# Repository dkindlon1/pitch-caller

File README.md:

# Pitch Caller

A pitch-calling engine for baseball coaches who don't know sequencing well. Each pitch it puts down a sign and a
spot (pitch type plus one of six targets), chosen at random from a mix weighted toward the calls that give up the
fewest expected runs. The mix keeps it hard to read. It tracks the pitcher's confidence in each pitch, learns each
hitter during the game, and flags when the pitcher may be done.

Levels: high school, college D3, college D1, and pro tables for comparison.

## How it decides

    Cost(pitch, spot | situation) = sum over outcomes  P(outcome) x [runs now + run value of the next state]

- **Run values** by level from real data: MLB 2010-15, 2026 NCAA conference team stats (D1, D3), MaxPreps 2026
  national varsity averages (high school). See `college_rates.py`, `hs_rates.py`, `run_tables.py`.
- **Outcome model**: where the pitch lands (command, confidence, level wildness, whether it's landing today), then
  swing, whiff, called strike, foul, contact quality, hit by pitch, wild pitch. Fitted so simulated games
  reproduce each level's real strikeout, walk, HBP and hit rates (`calib.py`, `fit_all.py`, `outcome_params.py`).
- **Calls**: each at-bat is solved once over count x the hitter's look, with the hitter's guess (what he's sitting on)
  settled at each count; the call is drawn from the low-cost calls inside a never-pick window, and randomness scales
  with the stakes of the count.
- **Coach rules built in**: get it over with off-speed only when that pitch is landing today; attack the zone at
  2-2; never re-call what he just shook off; nothing below the pitcher's trust line while he trusts something.

## The engine: v1.0, one version

There is one engine, with no flags or modes, in Python (`engine.py`, the reference) and JavaScript (`app/engine.js`,
copied to `web/lib/`). It is v0.8's at-bat planning (below) plus the v0.9 terms and the v1.0 fixes and fits
(`docs/PLAN_v1.0_2026-11-09.md`, build log `docs/BUILD_v1.0_REPORT.md`). `golden/golden_v10.py` and
`golden/golden_v10.js` check Python and JavaScript against one frozen reference (500 cases); `golden/fast.py` compares
the two live. The v0.7c call path and the other v0.9 leftovers were removed in v1.0 Step 6.

## Planning the at-bat (from v0.8)

v0.8 (spec: `docs/SPEC_v0.8.md`, amendments in its section 12) keeps the cost equation and adds what a pitching coach
thinks about between pitches:

- **What he's sitting on.** The hitter guesses a pitch and a height; the engine and the hitter settle at a
  quantal-response balance point each count, and a "fooled" read shifts his guess for the rest of the at-bat.
- **Planning ahead.** Each at-bat is solved once over count × the hitter's look (the speed and height he's tuned to),
  so a pitch is valued for what it sets up. A guardrail keeps every call within 0.010 runs of the best call on its own.
- **Timing, eye level, repeats, familiarity** by class from earlier at-bats today (replacing v0.7c's pairing and
  batters-faced terms), with Statcast-fitted sizes (`seq_fit.py`, `fit_v08.json`): timing surprise ships at half the
  guess, a change of eye level slightly *hurts* in MLB data, and tunneling ships on chase swings only (v1.0 D5:
  `beta_tun_chase` 0.310 fitted, `beta_tun_whiff` 0; the tunnel score showed no effect on whiffs).
- **The game situation.** Win expectancy and leverage tables (`we_tables.py`) blend runs with winning late in close
  games; typed batted balls with runner-on-third and double-play rules; the running game; an intentional-walk
  suggestion.
- **Today's umpire**, fatigue (speed and stuff, or radar), hitter grades (contact, power, eye) learned across games.
- **A why line** on every call.

Checks: `golden/golden_v10.*`, `tests.py`, `tests_v09_followups.py`, `readthrough/scenarios.py`, `app/budget_v08.js`,
`app/v08_e2e.js`. The v0.7c and v0.8 engines and their golden files are gone (v1.0 Step 6); `golden/golden_v09.json` stays as the historical v0.9 reference and the source of the golden inputs.
Build report (v0.8): `docs/BUILD_v0.8_REPORT.md`.

## Known limits (v1.0)

- **Runner advancement (#23, D10, skipped for 1.0):** a non-double-play ground out doesn't move a runner from first to
  second, and a single doesn't take a runner from first to third. Small run-value gaps; the simulator shares them.
- **Side-blind misses (D6, deferred):** a missed pitch misses up/down and in/off the zone, never specifically arm side or
  glove side.
- **Familiarity (#26, dropped):** the within-game familiarity term stays as fitted; the claim that it "erases the pitch"
  did not reproduce, and in-game hitter memory has one owner (#7).

## Watch prototype (opt-in)

Pitcher and catcher wristbands on Bangle.js 2 (plan: `docs/plans/PLAN_watch_prototype_2026-11-15.md`, review:
`docs/REVIEW_watch_prototype_plan_2026-11-15.md`). The coach taps **Accept** under the call (or Enter) and both watches show
the sign and the spot in words; a recorded pitch, a shake-off, his own call, undo or the third out clears them. Only where
the browser has Web Bluetooth (Chrome on a computer or Android) and the device opted in by opening the game app once
with `?watch=1` (`?watch=0` turns it off); everywhere else, the iPad included, nothing changes.

| File | What it is |
| --- | --- |
| `app/watch.js` | The link: up to two watches, one write queue each, message numbers, receipts and retries, reconnect, soak mode |
| `watch/bangle/pitchiq.app.js` | The watch app (its own Bluetooth service, data not code); install steps in `watch/bangle/README.md` |
| `app/watch_test.js`, `watch/bangle/test.js`, `app/watch_e2e.js` | The link against fake watches running the real watch core; the watch app against stand-in firmware; the page |

## Files

| File | What it is |
| --- | --- |
| `engine.py` | The engine, v1.0 (the reference; `app/engine.js` is its JavaScript twin): the at-bat solve and live call (`call_v08`), the outcome model, coach rules, the why line and intent label; one grade point = one SD of real pitchers (and hitters) at the level |
| `pitcher_lines.py`, `talent_spread.py`, `fit_spread.py`, `spread_params.py`, `spread_test.py` | Spread calibration: real 2026 per-pitcher lines, the true spread between pitchers, the fitted scales, and the check |
| `flags.py` | "Time for a change" flag |
| `simulate.py` | Full-game simulator with hidden hitter traits and pitch off-days; presets for pitcher and lineup types |
| `review.py` | Grades every call against coaching rules (wrong / questionable) and measures predictability |
| `batch.py`, `regrade.py`, `inputs_report.py` | Run many games and summarize them |
| `college_rates.py`, `hs_rates.py`, `run_tables.py` | Run values from real stats |
| `calib.py`, `fit_all.py`, `refit_mlb.py` | Fit the outcome model to real rates |
| `tests.py` | Regression checks (42 in v1.0), including the predictability grid (`grid_v10.py`) |
| `statcast_check.py` | The hitter-vs-pitch model against MLB Statcast pitches, by attack zone and count (`results/statcast_check.txt`) |
| `fuzz.py` | 29 logic and learning checks on thousands of random situations |
| `matrix/` | 21-setup test matrix: levels, pitcher types, lineups, input levels, shake-offs, coach overrides |
| `results/` | Latest logic-check and matrix reports |
| `app/` | Tablet prototype: `engine.js` (JavaScript port, verified against Python), `index.src.html`, built page in `dist/` |

## Run it

Python 3.11+ with `numpy` and `scipy`. Node 18+ for the app checks (Playwright for the browser test).

    python3 tests.py                                     # regression checks (42)
    python3 spread_test.py                               # calibrated spread between pitchers (about 2 minutes)
    python3 fuzz.py 3000 300                             # logic and learning checks
    LEVEL=college_d3 python3 batch.py runs/d3 1 10        # 10 simulated D3 games, graded
    STAFF=power LINEUP=fb_mashers LEVEL=hs python3 batch.py runs/x 1 10
    ./matrix/run.sh && python3 matrix/report.py           # the full matrix (about an hour)

    python3 golden/fast.py 40 && node golden/golden_v10.js  # JS engine must match Python exactly
    cd app && python3 build.py                             # builds dist/pitch-caller.html
    node app/smoke.js                                      # drives the page in a browser (from the repo root)

Simulator settings (environment variables): `LEVEL` (hs, college_d3, college_d1, mlb), `STAFF` (default, power,
finesse, two_pitch, lefty, four_pitch, shaky), `LINEUP` (default, strong, weak, lefty_heavy, switch, fb_mashers,
os_killers, late), `INPUTS` (1 results only, 2 plus contact, 3 plus hitter reads, 4 plus measured movement),
`NOISE` (share of optional entries logged wrong), `TRUE_MOVE`, `SHAKE`, `OVERRIDE`.

## Database and learning (app/)

Everything lives on the device in IndexedDB (`app/db.js`): our team, pitchers with their arsenals, catchers, opponents
and their hitters, pre-game check-ins, TrackMan/Rapsodo sessions, games, every pitch thrown, and the learned models.
Records carry ids and timestamps and are soft-deleted, so a sync service (Supabase or similar) can be added later
without changing the data. Back up and Restore on the Roster screen write and merge a JSON file (newer edits win).

**Every logged pitch stores** the pitcher, pitch, hitter, catcher, target, result, where it ended up (if logged), the
exact situation and inputs the engine used, and what the engine expected to happen.

**The flywheel** (`app/learner.js`, learner v2, spec in `docs/LEARNING_SPEC.md`): after End game, every pitch he has
thrown is replayed against what the engine expected, and each pitch's command and stuff are tracked game by game
(starting from the coach's grades, allowing for drift, a new season and changes the coach marks). The calls move toward
what's learned at most 0.15 a game and never more than 1.0 from the coach's grade unless he accepts a flag. Big
disagreements are flagged, not applied. A scoreboard compares learning with the coach's grades and switches learning off
if it predicts worse. Only the engine's own calls teach it. Hitters carry what they did against what the engine expected
across games. Check-ins set the day's starting feel per pitch and can lower his fatigue point.

**Imports** (`app/import.js`): TrackMan CSVs by its documented column names; Rapsodo by loose name matching (check the
first real file). Break and release side are normalised to arm side positive using his fastballs. Opponent hitter sheets.

| File | What it is |
| --- | --- |
| `app/db.js` | Database: stores, backup/restore, migration from the old saved state |
| `app/learn.js` | Learner v1 (now only check-ins, predictions and logging helpers in the app; its limits fixed in 1.1.0) |
| `app/import.js` | TrackMan, Rapsodo and hitter-sheet import |
| `app/roster.js` | Database glue and the Roster screen (inlined into the page by `build.py`) |
| `app/learn_test.js`, `db_test.js`, `import_test.js` | Node checks (`db_test.js` needs `npm i fake-indexeddb`) |
| `app/db_e2e.js` | Browser test of the whole loop, served over http; screenshots in `app/e2e_shots/` |
| `app/learner.js`, `app/worker.js` | Learner v2 (spec in `docs/LEARNING_SPEC.md`): replay, talent filter, traits, caps, flags, scoreboard. Drives the calls; runs after End game in a background worker. No trait passes the gate on v0.7b/c, so traits are off |
| `app/travel_e2e.js` | Browser check: travel ball in Setup, calls at that level, a coach's chase call at 3-1 graded against the rule |
| `app/replay_e2e.js`, `app/replay_check.js` | Proof that a charted game replays exactly from the raw log (browser game, then any backup) |
| `app/shadow.js`, `app/sim_backup.js` | Learner v2 scored against the coach's grades and what the app served, on a backup; seasons charted through the app from a hidden true pitcher |
| `app/worlds.js`, `app/worlds_test.js` | Simulated seasons played pitch by pitch, and the 13 worlds checks for learner v2 |
| `app/gate_test.js`, `app/gate_result.json` | The trait gate and its latest result |
| `app/same_engine_test.py` | Proves engine v0.7 with no traits and spread scales at 1 is identical to v0.6f (needs the old engine file as an argument) |

    cd app && node learn_test.js && node db_test.js && node import_test.js
    python3 build.py && node db_e2e.js

## Status

**Nov 6:** one engine, v0.9, no flags. See the top of this file and `docs/FOLLOWUPS_v0.9_REPORT.md`. The history below
is kept as it was.

Engine v0.7c (2026-11-03): 3-0 gets the tightest mix (an average arsenal throws about two fastballs in three there),
learning mode is scored the way calls are made, travel ball is a level (high school tables), impossible input gets a clear
error. Regression 19 of 19, logic 27 of 29 (same two explained), parity, spread, worlds 13 of 13, app tests all pass.

**Statcast check** (`statcast_check.py`, 2025 MLB, about 86,000 pitches): the engine's run values per zone are close in
many spots, but its hitter model is too flat. It has about half the real swing-and-miss rate in every zone and makes up
the strikeouts with too many chase swings, and in pitcher's counts it charges off-speed over the heart about a third of
what real hitters do (0.016 runs more than the edge, real 0.045). That's why "middle" stays in the two-strike mix.
Not yet refit.

Tested in simulation only. Engine v0.7b (spec section 18): command and stuff spread and the walk/strikeout link match
real 2026 pitchers; no chase target at 3-0 or 3-1. Regression checks 17 of 17, logic checks 27 of 29 (the two failures
are explained in the spec), learner worlds 13 of 13, spread checks all pass; reduced matrix (6 setups × 4 games) wrong
calls 0.3-4.9%. Open: amateur hitters' swing and chase behavior
is assumed MLB-like until real pitch-by-pitch data is available; HS spread is estimated from D3.

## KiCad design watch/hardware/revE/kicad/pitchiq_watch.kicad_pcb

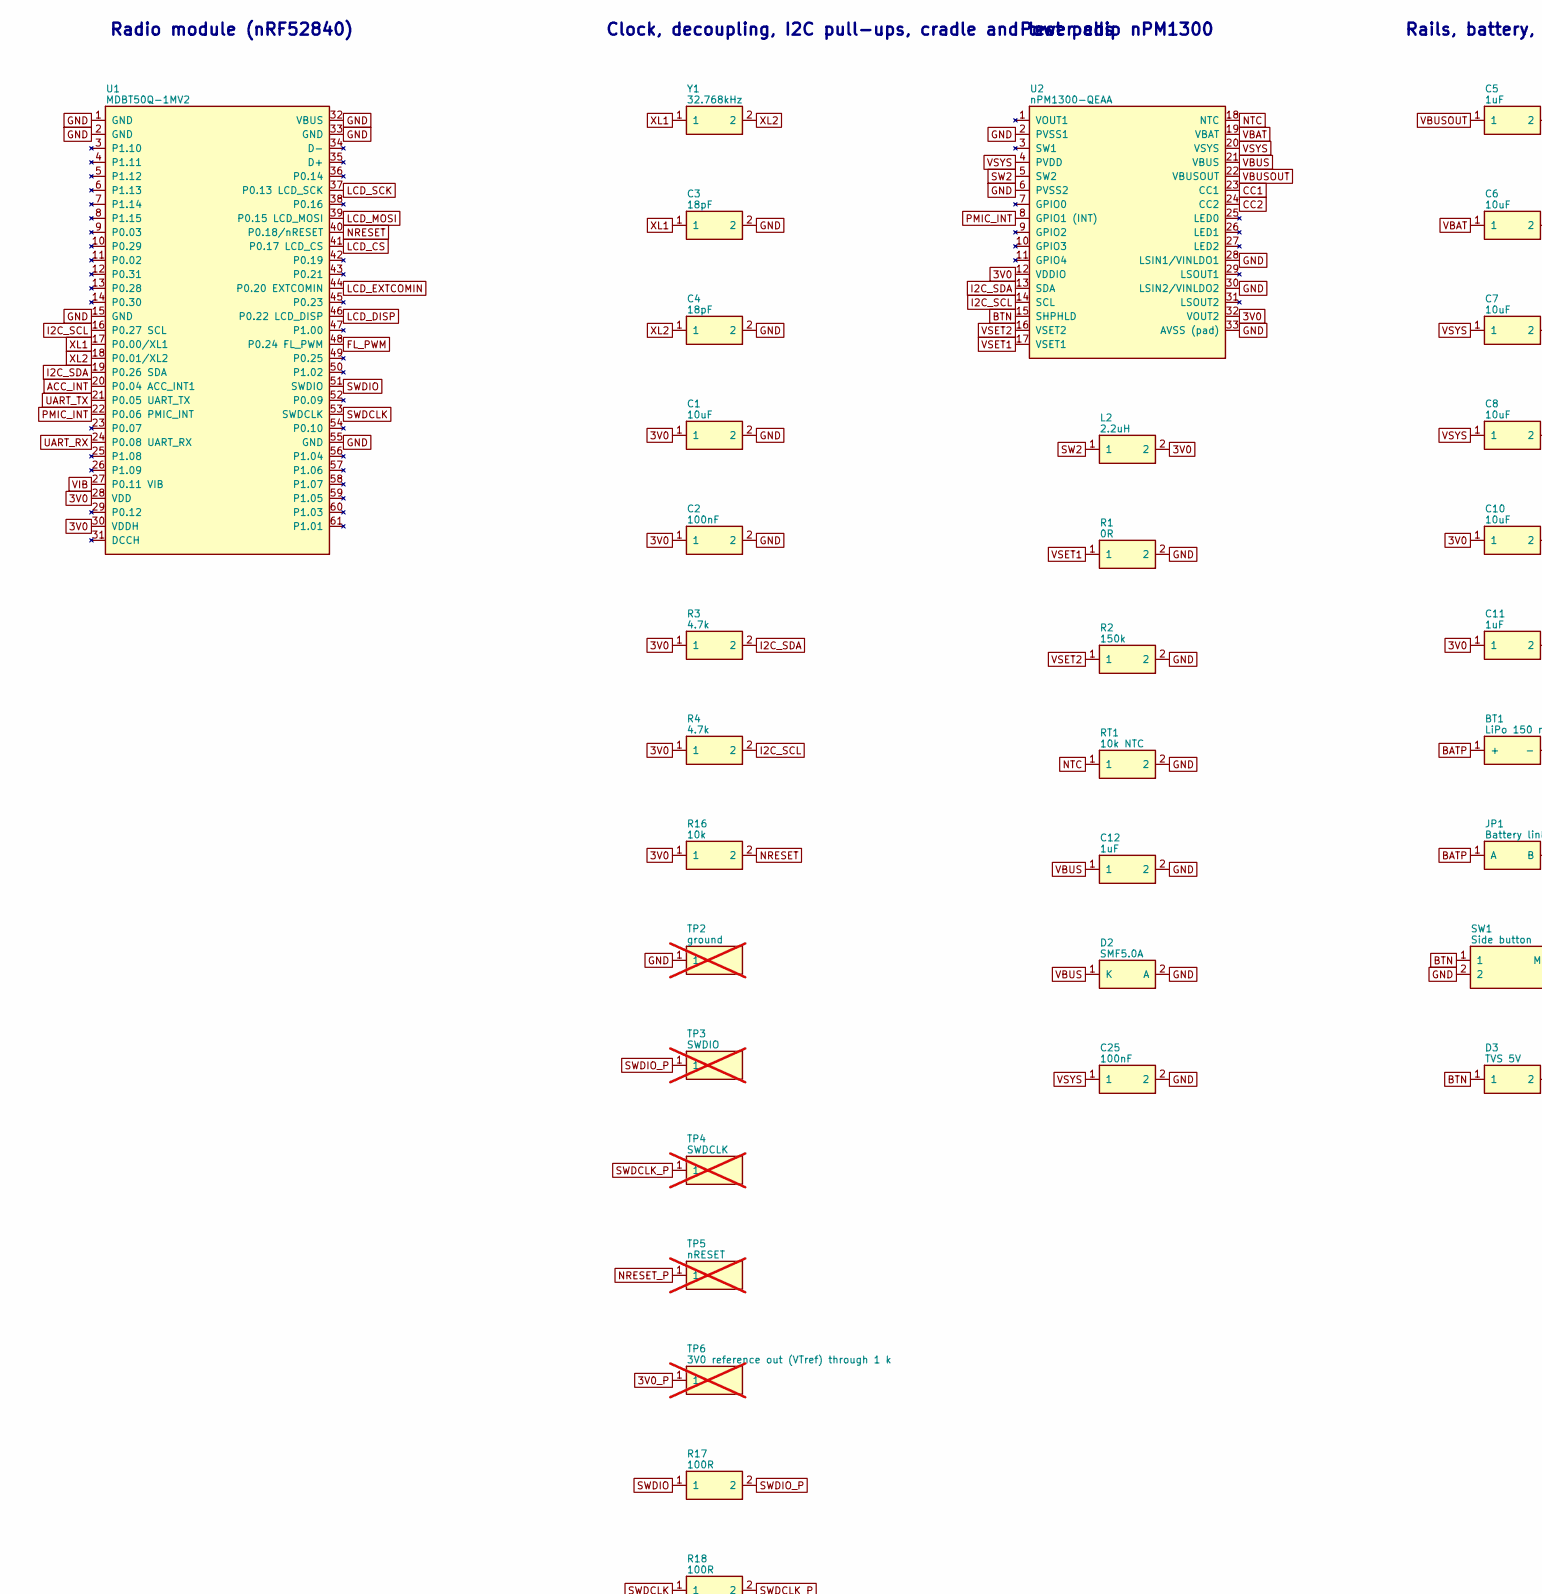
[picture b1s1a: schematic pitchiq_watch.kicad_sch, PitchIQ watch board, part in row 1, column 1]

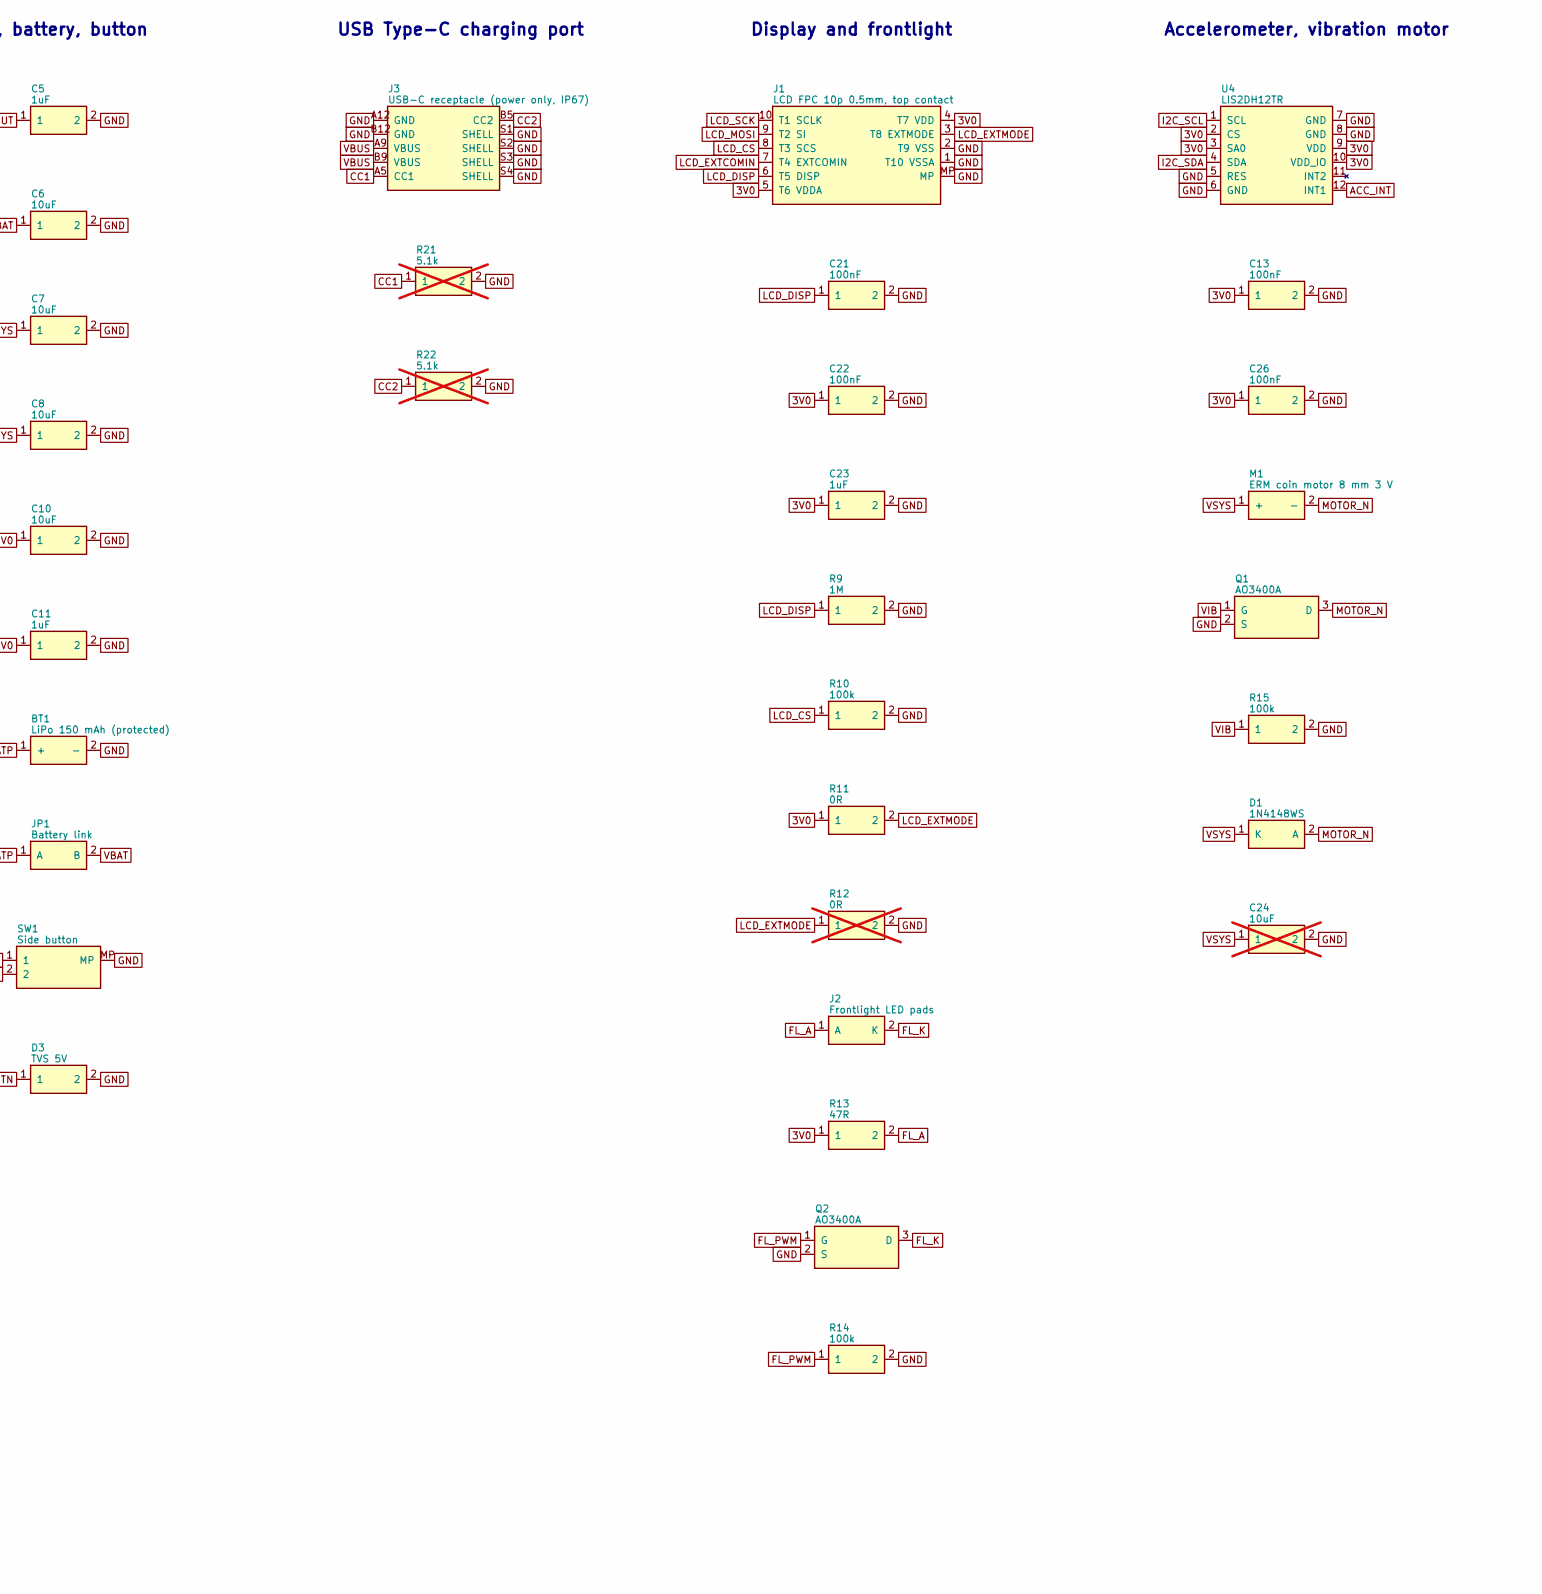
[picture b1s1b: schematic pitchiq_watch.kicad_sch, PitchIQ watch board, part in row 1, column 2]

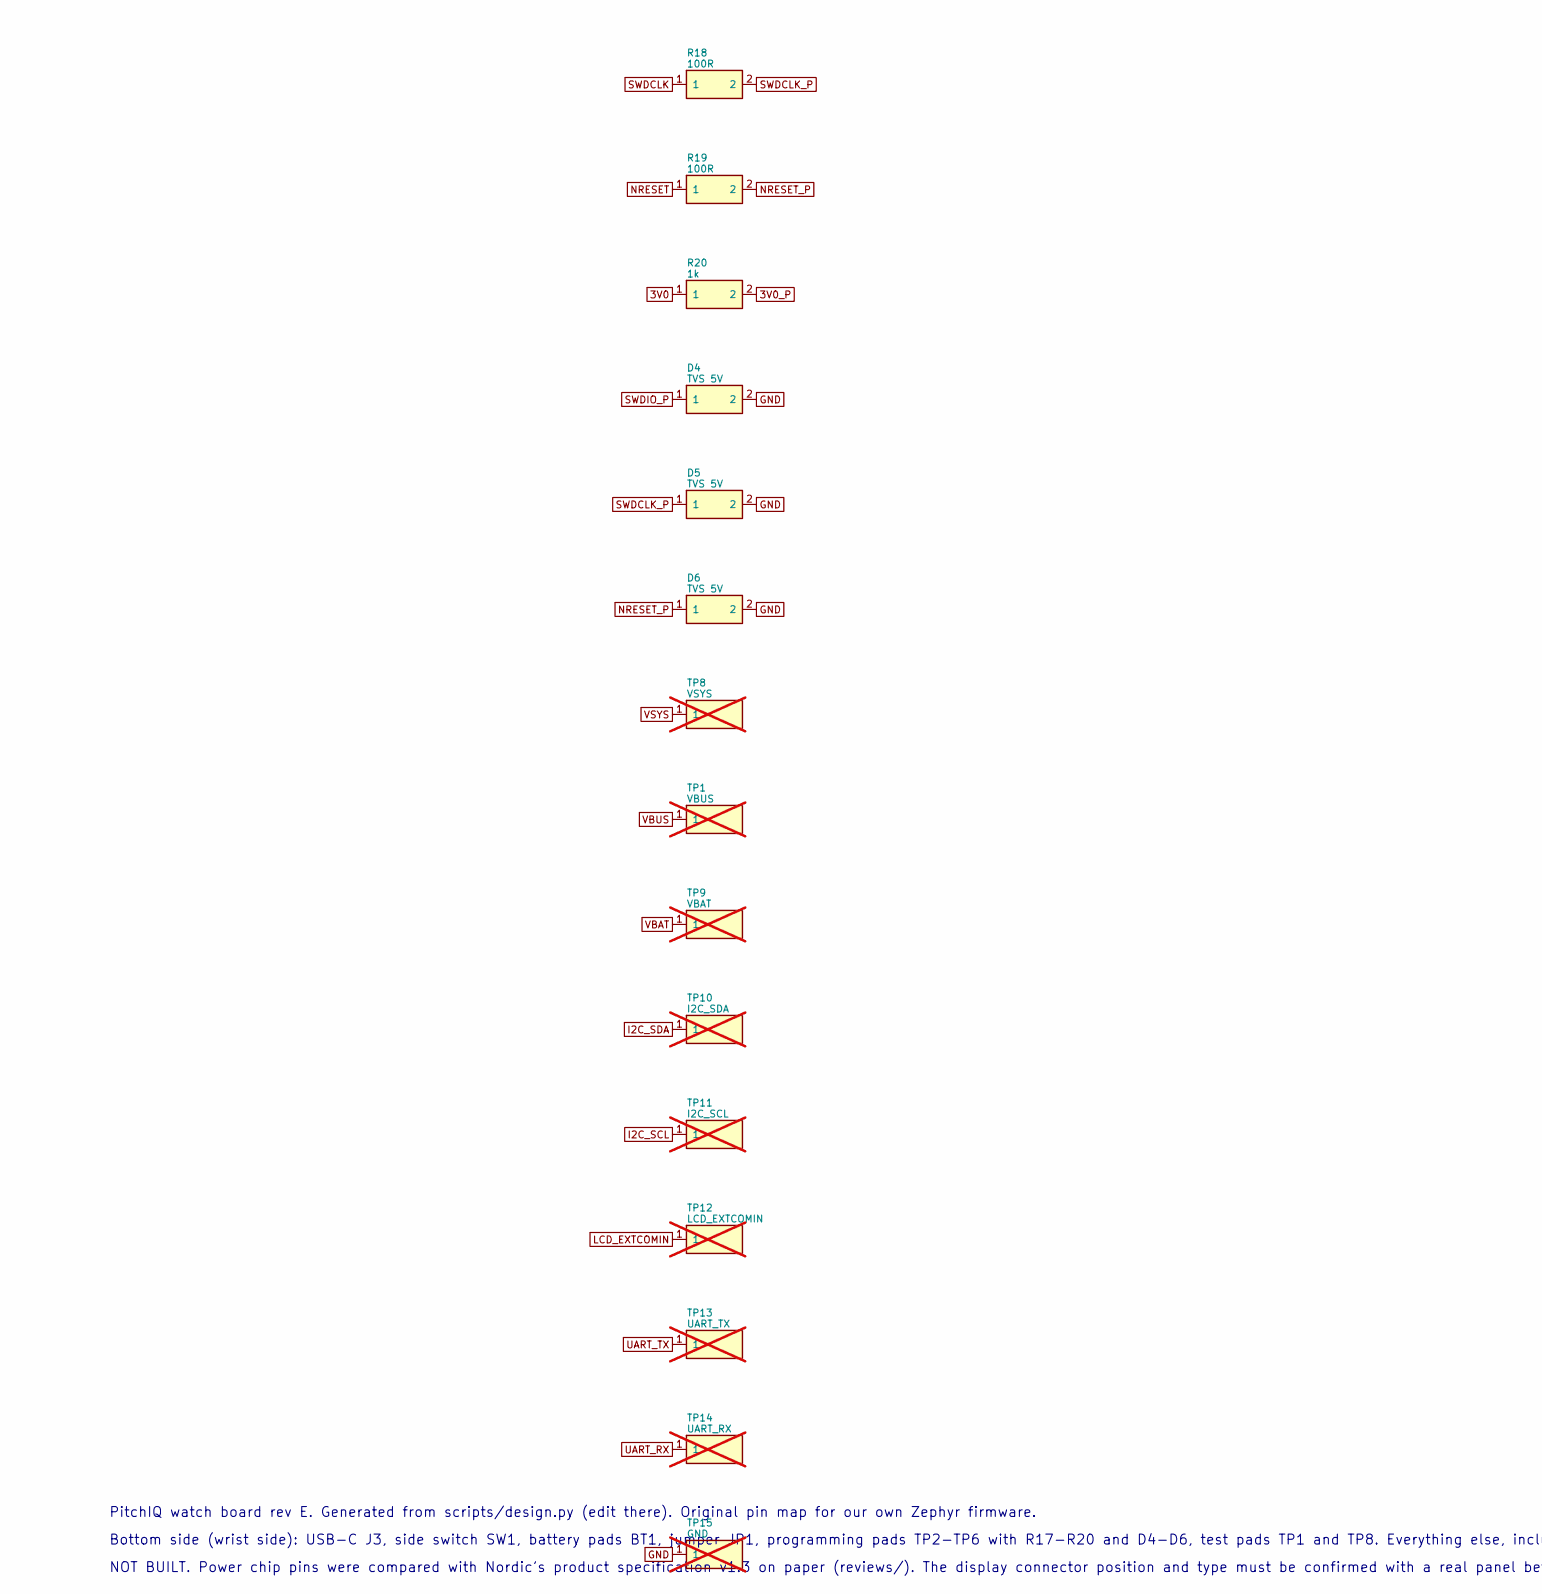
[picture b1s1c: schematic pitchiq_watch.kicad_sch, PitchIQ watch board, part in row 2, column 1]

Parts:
BT1: LiPo 150 mAh (protected); Pad_2x_wire; MPN 1317
C1, C6, C7, C8, C10: 10uF; C_0603_1608Metric; MPN CL10A106MA8NRNC; LCSC C96446
C2, C13, C21, C22, C25, C26: 100nF; C_0402_1005Metric; MPN CL05B104KO5NNNC; LCSC C1525
C3, C4: 18pF; C_0402_1005Metric; MPN CL05C180JB5NNNC; LCSC C307443
C5, C11, C12, C23: 1uF; C_0402_1005Metric; MPN CL05A105KA5NQNC; LCSC C52923
C24: 10uF; C_0603_1608Metric; MPN CL10A106MA8NRNC; LCSC C96446; not fitted
D1: 1N4148WS; D_SOD-323; MPN 1N4148WS; LCSC C2128
D2: SMF5.0A; D_SOD-123F; MPN SMF5.0A; LCSC C151296
D3, D4, D5, D6: TVS 5V; D_SOD-323; MPN PESD5V0S1BA; LCSC C2985486
J1: LCD FPC 10p 0.5mm, top contact; Hirose_FH12-10S-0.5SH_1x10-1MP_P0.50mm_Horizontal; MPN FH12A-10S-0.5SH(55)
J2: Frontlight LED pads; Pad_2x_wire_small; MPN (pads only)
J3: USB-C receptacle (power only, IP67); USB4715; MPN USB4715-GF-A; LCSC C6906846
JP1: Battery link; SolderJumper-2_P1.3mm_Open_RoundedPad1.0x1.5mm; MPN (solder bridge)
L2: 2.2uH; L_0805_2012Metric; MPN MLP2012H2R2MT0S1; LCSC C383369
M1: ERM coin motor 8 mm 3 V; Pad_2x_wire_small; MPN VCLP0820B004L
Q1, Q2: AO3400A; SOT-23; MPN AO3400A; LCSC C20917
R1, R11: 0R; R_0402_1005Metric; MPN 0402WGF0000TCE; LCSC C17168
R2: 150k; R_0402_1005Metric; MPN 0402WGF1503TCE; LCSC C25755
R3, R4: 4.7k; R_0402_1005Metric; MPN 0402WGF4701TCE; LCSC C25900
R9: 1M; R_0402_1005Metric; MPN 0402WGF1004TCE; LCSC C26083
R10, R14, R15: 100k; R_0402_1005Metric; MPN 0402WGF1003TCE; LCSC C25741
R12: 0R; R_0402_1005Metric; MPN 0402WGF0000TCE; LCSC C17168; not fitted
R13: 47R; R_0402_1005Metric; MPN 0402WGF470JTCE; LCSC C25118
R16: 10k; R_0402_1005Metric; MPN 0402WGF1002TCE; LCSC C25744
R17, R18, R19: 100R; R_0402_1005Metric; MPN 0402WGF1000TCE; LCSC C25076
R20: 1k; R_0402_1005Metric; MPN 0402WGF1001TCE; LCSC C11702
R21, R22: 5.1k; R_0402_1005Metric; MPN 0402WGF5101TCE; LCSC C25905; not fitted
RT1: 10k NTC; R_0402_1005Metric; MPN NCP15XH103F03RC; LCSC C77131
SW1: Side button; SW_Push_1P1T-MP_NO_Horizontal_Alps_SKRTLAE010; MPN SKRTLAE010; LCSC C110293
TP1: VBUS; TestPoint_Pad_D1.5mm; not fitted
TP2: ground; TestPoint_Pad_D1.5mm; not fitted
TP3: SWDIO; TestPoint_Pad_D1.5mm; not fitted
TP4: SWDCLK; TestPoint_Pad_D1.5mm; not fitted
TP5: nRESET; TestPoint_Pad_D1.5mm; not fitted
TP6: 3V0 reference out (VTref) through 1 k; TestPoint_Pad_D1.5mm; not fitted
TP8: VSYS; TestPoint_Pad_D1.5mm; not fitted
TP9: VBAT; TestPoint_Pad_D1.0mm; not fitted
TP10: I2C_SDA; TestPoint_Pad_D1.0mm; not fitted
TP11: I2C_SCL; TestPoint_Pad_D1.0mm; not fitted
TP12: LCD_EXTCOMIN; TestPoint_Pad_D1.0mm; not fitted
TP13: UART_TX; TestPoint_Pad_D1.0mm; not fitted
TP14: UART_RX; TestPoint_Pad_D1.0mm; not fitted
TP15: GND; TestPoint_Pad_D1.0mm; not fitted
U1: MDBT50Q-1MV2; Raytac_MDBT50Q; MPN MDBT50Q-1MV2; LCSC C5118826
U2: nPM1300-QEAA; QFN-32-1EP_5x5mm_P0.5mm_EP3.45x3.45mm; MPN NPM1300-QEAA-R7; LCSC C7501206
U4: LIS2DH12TR; LGA-12_2x2mm_P0.5mm; MPN LIS2DH12TR; LCSC C110926
Y1: 32.768kHz; Crystal_SMD_3215-2Pin_3.2x1.5mm; MPN Q13FC13500004; LCSC C32346

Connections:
3V0: C1.1, C2.1, C10.1, C11.1, C13.1, C22.1, C23.1, C26.1, J1.4 (T7 VDD), J1.5 (T6 VDDA), L2.2, R3.1, R4.1, R11.1, R13.1, R16.1, R20.1, U1.28 (VDD), U1.30 (VDDH), U2.12 (VDDIO), U2.32 (VOUT2), U4.2 (CS), U4.3 (SA0), U4.9 (VDD), U4.10 (VDD_IO)
3V0_P: R20.2, TP6.1
ACC_INT: U1.20 (P0.04 ACC_INT1), U4.12 (INT1)
BATP: BT1.1 (+), JP1.1 (A)
BTN: D3.1, SW1.1, U2.15 (SHPHLD)
CC1: J3.A5 (CC1), R21.1, U2.23 (CC1)
CC2: J3.B5 (CC2), R22.1, U2.24 (CC2)
FL_A: J2.1 (A), R13.2
FL_K: J2.2 (K), Q2.3 (D)
FL_PWM: Q2.1 (G), R14.1, U1.48 (P0.24 FL_PWM)
GND: BT1.2 (-), C1.2, C2.2, C3.2, C4.2, C5.2, C6.2, C7.2, C8.2, C10.2, C11.2, C12.2, C13.2, C21.2, C22.2, C23.2, C24.2, C25.2, C26.2, D2.2 (A), D3.2, D4.2, D5.2, D6.2, J1.1 (T10 VSSA), J1.2 (T9 VSS), J1.MP, J3.A12 (GND), J3.B12 (GND), J3.S1 (SHELL), J3.S2 (SHELL), J3.S3 (SHELL), J3.S4 (SHELL), Q1.2 (S), Q2.2 (S), R1.2, R2.2, R9.2, R10.2, R12.2, R14.2, R15.2, R21.2, R22.2, RT1.2, SW1.2, SW1.MP, TP2.1, TP15.1, U1.1 (GND), U1.2 (GND), U1.15 (GND), U1.32 (VBUS), U1.33 (GND), U1.55 (GND), U2.2 (PVSS1), U2.6 (PVSS2), U2.28 (LSIN1/VINLDO1), U2.30 (LSIN2/VINLDO2), U2.33 (AVSS (pad)), U4.5 (RES), U4.6 (GND), U4.7 (GND), U4.8 (GND)
I2C_SCL: R4.2, TP11.1, U1.16 (P0.27 SCL), U2.14 (SCL), U4.1 (SCL)
I2C_SDA: R3.2, TP10.1, U1.19 (P0.26 SDA), U2.13 (SDA), U4.4 (SDA)
LCD_CS: J1.8 (T3 SCS), R10.1, U1.41 (P0.17 LCD_CS)
LCD_DISP: C21.1, J1.6 (T5 DISP), R9.1, U1.46 (P0.22 LCD_DISP)
LCD_EXTCOMIN: J1.7 (T4 EXTCOMIN), TP12.1, U1.44 (P0.20 EXTCOMIN)
LCD_EXTMODE: J1.3 (T8 EXTMODE), R11.2, R12.1
LCD_MOSI: J1.9 (T2 SI), U1.39 (P0.15 LCD_MOSI)
LCD_SCK: J1.10 (T1 SCLK), U1.37 (P0.13 LCD_SCK)
MOTOR_N: D1.2 (A), M1.2 (-), Q1.3 (D)
NRESET: R16.2, R19.1, U1.40 (P0.18/nRESET)
NRESET_P: D6.1, R19.2, TP5.1
NTC: RT1.1, U2.18 (NTC)
PMIC_INT: U1.22 (P0.06 PMIC_INT), U2.8 (GPIO1 (INT))
SW2: L2.1, U2.5 (SW2)
SWDCLK: R18.1, U1.53 (SWDCLK)
SWDCLK_P: D5.1, R18.2, TP4.1
SWDIO: R17.1, U1.51 (SWDIO)
SWDIO_P: D4.1, R17.2, TP3.1
UART_RX: TP14.1, U1.24 (P0.08 UART_RX)
UART_TX: TP13.1, U1.21 (P0.05 UART_TX)
VBAT: C6.1, JP1.2 (B), TP9.1, U2.19 (VBAT)
VBUS: C12.1, D2.1 (K), J3.A9 (VBUS), J3.B9 (VBUS), TP1.1, U2.21 (VBUS)
VBUSOUT: C5.1, U2.22 (VBUSOUT)
VIB: Q1.1 (G), R15.1, U1.27 (P0.11 VIB)
VSET1: R1.1, U2.17 (VSET1)
VSET2: R2.1, U2.16 (VSET2)
VSYS: C7.1, C8.1, C24.1, C25.1, D1.1 (K), M1.1 (+), TP8.1, U2.4 (PVDD), U2.20 (VSYS)
XL1: C3.1, U1.17 (P0.00/XL1), Y1.1
XL2: C4.1, U1.18 (P0.01/XL2), Y1.2

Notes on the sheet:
Radio module (nRF52840)
Clock, decoupling, I2C pull-ups, cradle and test pads
Power chip nPM1300
Rails, battery, button
USB Type-C charging port
Display and frontlight
Accelerometer, vibration motor
PitchIQ watch board rev E. Generated from scripts/design.py (edit there). Original pin map for our own Zephyr firmware.
Bottom side (wrist side): USB-C J3, side switch SW1, battery pads BT1, jumper JP1, programming pads TP2-TP6 with R17-R20 and D4-D6, test pads TP1 and TP8. Everything else, including bring-up pads TP9-TP15, is on the top side.
NOT BUILT. Power chip pins were compared with Nordic's product specification v1.3 on paper (reviews/). The display connector position and type must be confirmed with a real panel before ordering.

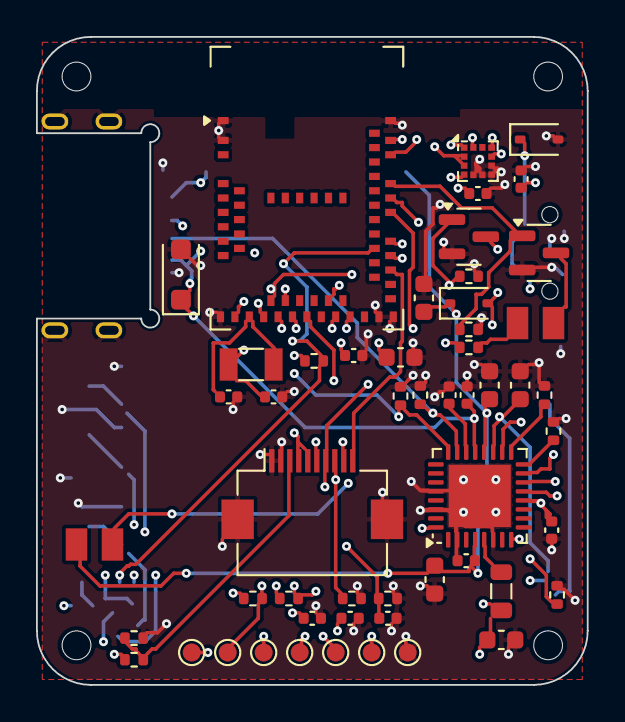
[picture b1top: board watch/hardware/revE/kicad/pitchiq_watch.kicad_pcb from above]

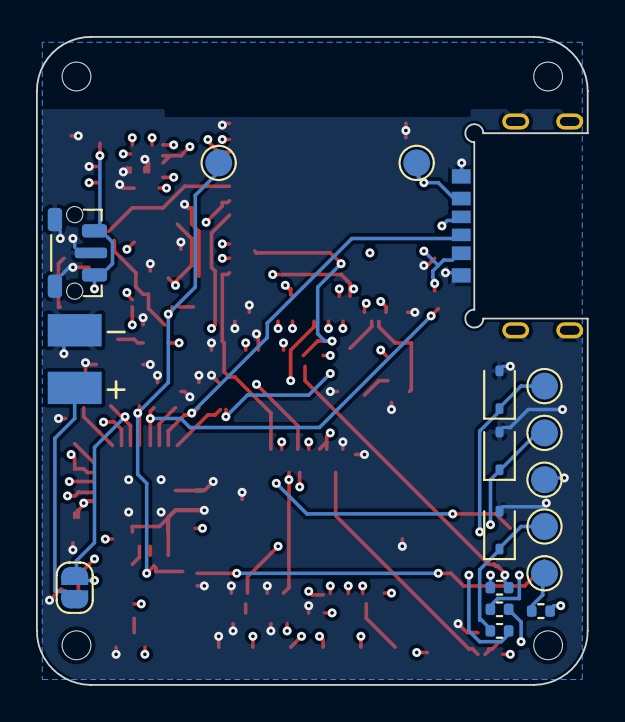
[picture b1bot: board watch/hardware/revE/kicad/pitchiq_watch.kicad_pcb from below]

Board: 6 copper layers, 30.6 x 36.0 mm, 75 parts (18 on the bottom side), 40 nets.

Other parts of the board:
H1, H2, H3, H4: 1.6 mm hole; Hole_1.6mm_NPTH

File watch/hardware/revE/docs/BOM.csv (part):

Refs,Qty,Value,Function,Manufacturer,MPN,Footprint,LCSC,Assembly,USD each @1,USD each @~100,Price status,Buy / source
BT1,1,LiPo 150 mAh (protected),"3.7 V 150 mAh 402025 cell with protection circuit, under the board (wrist side); leads soldered to pads",Adafruit,1317,Pad_2x_wire,-,hand-soldered after SMT,5.9500,4.7600,seen,https://www.adafruit.com/products/1317
"C1,C6,C7,C8,C10",5,10uF,"module bulk decoupling, next to VDD/VDDH pads (25 V part, as in Nordic's bill of materials: keeps more of its capacitance at 4-5 V than the 10 V part used up to rev D); battery node (25 V part, as in Nordic's bill of materials: keeps more of its capacitance at 4-5 V than the 10 V part used up to rev D); system node (25 V part, as in Nordic's bill of materials: keeps more of its capacitance at 4-5 V than the 10 V part used up to rev D); buck input (PVDD) (25 V part, as in Nordic's bill of materials: keeps more of its capacitance at 4-5 V than the 10 V part used up to rev D); BUCK2 output (25 V part, as in Nordic's bill of materials: keeps more of its capacitance at 4-5 V than the 10 V part used up to rev D)",Samsung,CL10A106MA8NRNC,C_0603_1608Metric,C96446,SMT,0.0100,0.0030,est (Basic parts seen from $0.0005-0.01),https://www.lcsc.com/product-detail/C96446.html
"C2,C13,C21,C22,C25,C26",6,100nF,"module decoupling; accelerometer decoupling, Vdd (pin 9); Sharp fig. 9-1: DISP to VSS; Sharp fig. 9-1: VDDA; PVDD high-frequency bypass, placed 1 mm from the PVDD and PVSS1 pins; accelerometer decoupling, Vdd_IO (pin 10): ST shows one capacitor per supply pin",Samsung,CL05B104KO5NNNC,C_0402_1005Metric,C1525,SMT,0.0100,0.0030,est (Basic parts seen from $0.0005-0.01),https://www.lcsc.com/product-detail/C1525.html
"C3,C4",2,18pF,crystal load: 2 x (12.5 pF - ~3.5 pF stray),Samsung,CL05C180JB5NNNC,C_0402_1005Metric,C307443,SMT,0.0100,0.0030,est (Basic parts seen from $0.0005-0.01),https://www.lcsc.com/product-detail/C307443.html
"C5,C11,C12,C23",4,1uF,VBUSOUT bypass: 1 uF as in Nordic's bill of materials (PS v1.3); PMIC VDDIO; VBUS input: 1 uF 25 V as in Nordic's bill of materials (the VBUS pin survives 22 V; keeps the capacitance a USB source sees at attach small); Sharp fig. 9-1: VDD,Samsung,CL05A105KA5NQNC,C_0402_1005Metric,C52923,SMT,0.0100,0.0030,est (Basic parts seen from $0.0005-0.01),https://www.lcsc.com/product-detail/C52923.html
C24,1,10uF,"optional reservoir next to the motor switch. NOT fitted on the first boards: Nordic specifies 10 uF on VSYS and extra capacitance there makes start-up from a 100 mA USB source harder (25 V part, as in Nordic's bill of materials: keeps more of its capacitance at 4-5 V than the 10 V part used up to rev D)",Samsung,CL10A106MA8NRNC,C_0603_1608Metric,C96446,DNP (not fitted),0.0100,0.0030,est (Basic parts seen from $0.0005-0.01),https://www.lcsc.com/product-detail/C96446.html
D1,1,1N4148WS,motor flyback diode,various,1N4148WS,D_SOD-323,C2128,SMT,0.0053,0.0053,seen (from-price),https://www.lcsc.com/product-detail/C2128.html
D2,1,SMF5.0A,"USB VBUS surge clamp at the connector: 5 V stand-off, 9.2 V clamp (the power chip itself survives 22 V on VBUS). A 9 V or 12 V charger would overload it: 5 V chargers only",Littelfuse,SMF5.0A,D_SOD-123F,C151296,SMT,0.0546,0.0546,"seen (from-price, LCSC, 56,440 in stock)",https://www.lcsc.com/product-detail/C151296.html
"D3,D4,D5,D6",4,TVS 5V,button ESD clamp (finger-touched); programming-pad ESD clamp (about 35 pF: fine for SWD at 1 MHz through 100R),DOWO (Nexperia original),PESD5V0S1BA,D_SOD-323,C2985486,SMT,0.0125,0.0125,seen (from-price),https://jlcpcb.com/partdetail/C2985486
J1,1,"LCD FPC 10p 0.5mm, top contact","ZIF FPC connector, TOP contact (the A in FH12A). Hand-fitted or consigned: no LCSC number found. Land pattern assumed equal to the bottom-contact FH12-10S footprint used here (same series; not checked on Hirose's drawing)",Hirose,FH12A-10S-0.5SH(55),Hirose_FH12-10S-0.5SH_1x10-1MP_P0.50mm_Horizontal,-,hand-soldered after SMT,0.0000,0.0000,n/a,https://www.digikey.com/en/products/detail/hirose-electric-c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
J2,1,Frontlight LED pads,for an Azumo frontlight LED tail (5 mA typ at 3.0 V); unused with a bare panel,-,(pads only),Pad_2x_wire_small,-,hand-soldered after SMT,0.0000,0.0000,n/a,LCSC number not verified: search the MPN
J3,1,"USB-C receptacle (power only, IP67)","waterproof USB Type-C, charging only; gasket USBTJ-04 is fitted after soldering (kit: USB4715-GF-A-KIT, C5984345). LCSC out of stock Nov 23: buy at Mouser and consign",GCT,USB4715-GF-A,USB4715,C6906846,hand-soldered after SMT,1.6100,1.1700,"seen (Mouser via Octopart, 2,382 in stock; LCSC out of stock)",https://octopart.com/part/gct/USB4715-GF-A
JP1,1,Battery link,open until final assembly; bridge with solder last,-,(solder bridge),SolderJumper-2_P1.3mm_Open_RoundedPad1.0x1.5mm,-,hand-soldered after SMT,0.0000,0.0000,n/a,LCSC number not verified: search the MPN
L2,1,2.2uH,"buck inductor 2.2 uH, DCR 150 mOhm typ, 1 A rated (saturation current not published; alternative Murata DFE201610E-2R2M C337891 needs a 2016 footprint)",TDK,MLP2012H2R2MT0S1,L_0805_2012Metric,C383369,SMT,0.0500,0.0300,est,https://www.lcsc.com/product-detail/C383369.html
M1,1,ERM coin motor 8 mm 3 V,"8.0 x 2.1 mm coin vibration motor, 2.7-4.0 V, 35 mA max, adhesive backed, leads soldered to pads (firmware caps the duty: VSYS can exceed 4.0 V)",Vybronics,VCLP0820B004L,Pad_2x_wire_small,-,hand-soldered after SMT,3.1500,2.4713,"seen (DigiKey, 1,766 in stock)",https://www.digikey.com/en/products/detail/vybronics-inc/VCL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
"Q1,Q2",2,AO3400A,motor low-side switch (PWM); frontlight low-side switch (PWM),Alpha & Omega,AO3400A,SOT-23,C20917,SMT,0.0429,0.0429,seen (from-price),https://jlcpcb.com/partdetail/C20917
"R1,R11",2,0R,VSET1 to ground = BUCK1 off at start-up (nothing uses 1.8 V in rev C; firmware never enables it). L1/C9 stay fitted so SW1/VOUT1 are terminated exactly as on Nordic's evaluation kit; fit 47k here to get 1.8 V back; EXTMODE high: COM inversion from the EXTCOMIN pin,UNI-ROYAL,0402WGF0000TCE,R_0402_1005Metric,C17168,SMT,0.0100,0.0030,est (Basic parts seen from $0.0005-0.01),https://www.lcsc.com/product-detail/C17168.html
R2,1,150k,BUCK2 start-up voltage = 3.0 V (nPM1300 VSET table),UNI-ROYAL,0402WGF1503TCE,R_0402_1005Metric,C25755,SMT,0.0100,0.0030,est (Basic parts seen from $0.0005-0.01),https://www.lcsc.com/product-detail/C25755.html
"R3,R4",2,4.7k,I2C pull-up,UNI-ROYAL,0402WGF4701TCE,R_0402_1005Metric,C25900,SMT,0.0100,0.0030,est (Basic parts seen from $0.0005-0.01),https://www.lcsc.com/product-detail/C25900.html
R9,1,1M,"display off in reset (1 M: DISP is high all the time, so this resistor is a standing 3 uA load)",UNI-ROYAL,0402WGF1004TCE,R_0402_1005Metric,C26083,SMT,0.0100,0.0030,est (Basic parts seen from $0.0005-0.01),https://www.lcsc.com/product-detail/C26083.html
"R10,R14,R15",3,100k,LCD deselected in reset (SCS active high); frontlight off in reset; motor off in reset,UNI-ROYAL,0402WGF1003TCE,R_0402_1005Metric,C25741,SMT,0.0100,0.0030,est (Basic parts seen from $0.0005-0.01),https://www.lcsc.com/product-detail/C25741.html
R12,1,0R,"alternative: EXTMODE low, COM inversion by serial flag (fit instead of R11)",UNI-ROYAL,0402WGF0000TCE,R_0402_1005Metric,C17168,DNP (not fitted),0.0100,0.0030,est (Basic parts seen from $0.0005-0.01),https://www.lcsc.com/product-detail/C17168.html
R13,1,47R,frontlight LED current limit (value to confirm on the first frontlit unit),UNI-ROYAL,0402WGF470JTCE,R_0402_1005Metric,C25118,SMT,0.0100,0.0030,est (Basic parts seen from $0.0005-0.01),https://www.lcsc.com/product-detail/C25118.html
R16,1,10k,reset pull-up (pin is a GPIO until firmware enables pin reset),UNI-ROYAL,0402WGF1002TCE,R_0402_1005Metric,C25744,SMT,0.0100,0.0030,est (Basic parts seen from $0.0005-0.01),https://www.lcsc.com/product-detail/C25744.html
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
